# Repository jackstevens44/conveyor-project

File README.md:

# Conveyor Project

<!-- Replace this paragraph with a short description of the conveyor, what it is
designed to do, and its current development status. -->

This project is a compact conveyor system featuring a custom-designed controller PCB and 3D-printable mechanical components. I created it to gain hands-on experience with PCB design, electronics integration, mechanical design, rapid prototyping, and design-for-manufacturing.

## Project status

<!-- Examples: Planning, Prototype, Testing, or Complete. -->

**Status:** Prototype

## Repository contents

```text
conveyor-project/
├── pcb-files/                 KiCad design and fabrication files
│   ├── NewConveyorPCB.kicad_pro
│   ├── NewConveyorPCB.kicad_sch
│   ├── NewConveyorPCB.kicad_pcb
│   └── fab-files/gerbers.zip
├── stl-files/                 3D-printable mechanical parts
│   ├── conveyor-base-parts/
│   │   ├── BearingSlot.stl
│   │   ├── ConveyorBase.stl
│   │   └── MotorBase.stl
│   ├── MotorWheel.stl
│   ├── Sprocket.stl
│   ├── SprocketPin.stl
│   └── TreadLink.stl
├── code/                      Arduino code to control conveyor
└── README.md
```

## Requirements

<!-- Add versions when they are known. -->

- [KiCad](https://www.kicad.org/) to view or edit the PCB design
- A slicer and 3D printer for the STL parts
- Electronic components listed in the PCB bill of materials
- Motor, fasteners, wiring, and power supply

## Bill of materials

<!-- Replace this table with the actual parts list. Add a BOM export to
pcb-files/ if the list becomes long. -->

| Item | Quantity | Specification | Notes |
| --- | ---: | --- | --- |
| Motor | 1 | 5V DC Motor | [Digikey](https://www.digikey.com/en/products/detail/pololu/992/10449920) |
| Motor Driver | 1 | L293D | [Digikey](https://www.digikey.com/en/products/detail/stmicroelectronics/L293D/634700) |
| Arduino Nano | 1 | ABX00143 | [Digikey](https://www.digikey.com/en/products/detail/arduino/ABX00143/26766495) |
| 2 Position Terminal Blocks | 4 | TB002-599-02BE | [Digikey](https://www.digikey.com/en/products/detail/same-sky-formerly-cui-devices/TB002-500-02BE/10064069) |
| 4 Position Terminal Blocks | 3 | OSTTC042162 | [Digikey](https://www.digikey.com/en/products/detail/on-shore-technology-inc/OSTTC042162/614560) |
| Power supply | 1 | 5V DC Power Supply | [Amazon](https://www.amazon.com/Adjustable-Switching-Regulated-Adjustments-Jesverty/dp/B09YSJQWRG/ref=sr_1_9?crid=RU2I6P17LDUR&dib=eyJ2IjoiMSJ9.bpne59jAEmaTFwmIsQCQhTqgw4IQY65Dw4FDdB8OQz_Ecffxi1TowvI5zsghytbijl_1j7_s0npvxgVQFqhbWMT10DBirUDh4-yq3dJqWEhJmdyZwxivPJMaoJ1KstsehQq5iAvTCPxRA2gXOBRJsTDN7kXZ_Kgxwffos8XqOIRSXc5FngmeqCCIJYCrZ_1-oBqjrCkD9KUe5rgq8wMdk-KiZEaG6KIPqqcH2dt3D-8.EnnGaUa-Mi3bt2TU4QdSq8au0XoTXh95RY_4BBbdKmI&dib_tag=se&keywords=5v%2Bpower%2Bsupply%2Belectronics&qid=1785630137&sprefix=5v%2Bpower%2Bsupply%2Belectronics%2Caps%2C166&sr=8-9&th=1)|
| PCB | 1 | NewConveyorPCB | [JLCPCB](https://cart.jlcpcb.com/quote?stencilLayer=2&stencilWidth=100&stencilLength=100&stencilCounts=5&plateType=1&spm=Jlcpcb.Homepage.1010) |
| Conveyor base | 1 | 3D printed | `ConveyorBase.stl` |
| Motor Base | 1 | 3D printed | `MotorBase.stl` |
| Bearing slot | 4 | 3D printed | `BearingSlot.stl` |
| Motor wheel | 1 | 3D printed | `MotorWheel.stl` |
| Sprocket | 2 | 3D printed | `Sprocket.stl` |
| Sprocket pin | 2 | 3D printed | `SprocketPin.stl` |
| Tread link | 28 | 3D printed | `TreadLink.stl` |
| Ball Bearings | 4 | Any bearing that meets required dimensions | [Amazon](https://www.amazon.com/dp/B09PKD8QZZ?ref=ppx_yo2ov_dt_b_fed_asin_title&th=1) |
| Dowel Pins | 27 | 1/8" diameter 2-1/2" length | [McMaster](https://www.mcmaster.com/90145A487/) |
| Motor Band | 1 | TBD | TBD |

## Fabrication

1. Use any PCB fabrication company. JLCPCB is cheap and easy to use.

### PCB

1. Open `pcb-files/NewConveyorPCB.kicad_pro` in KiCad to review or modify the design.
2. Use `pcb-files/fab-files/gerbers.zip` when ordering the PCB.
3. Confirm the board dimensions, layer stack, drill files, and design rules with the manufacturer before ordering.

<!-- Add PCB manufacturer settings, component placement notes, and assembly
instructions here. -->

### 3D-printed parts

The printable models are in `stl-files/`.

## Assembly

<!-- Replace these placeholders with the tested assembly sequence. Photos or a
diagram are especially useful here. -->

1. Print and inspect all mechanical parts.
2. Solder components and test PCB.
3. Install the motor and motor wheel in the conveyor base.
4. Assemble the sprockets and tread links.
5. Connect the electronics and verify polarity before applying power.
6. Upload conveyor controller program to the Arduino Nano.
7. Test at low speed and adjust alignment and tension as needed.

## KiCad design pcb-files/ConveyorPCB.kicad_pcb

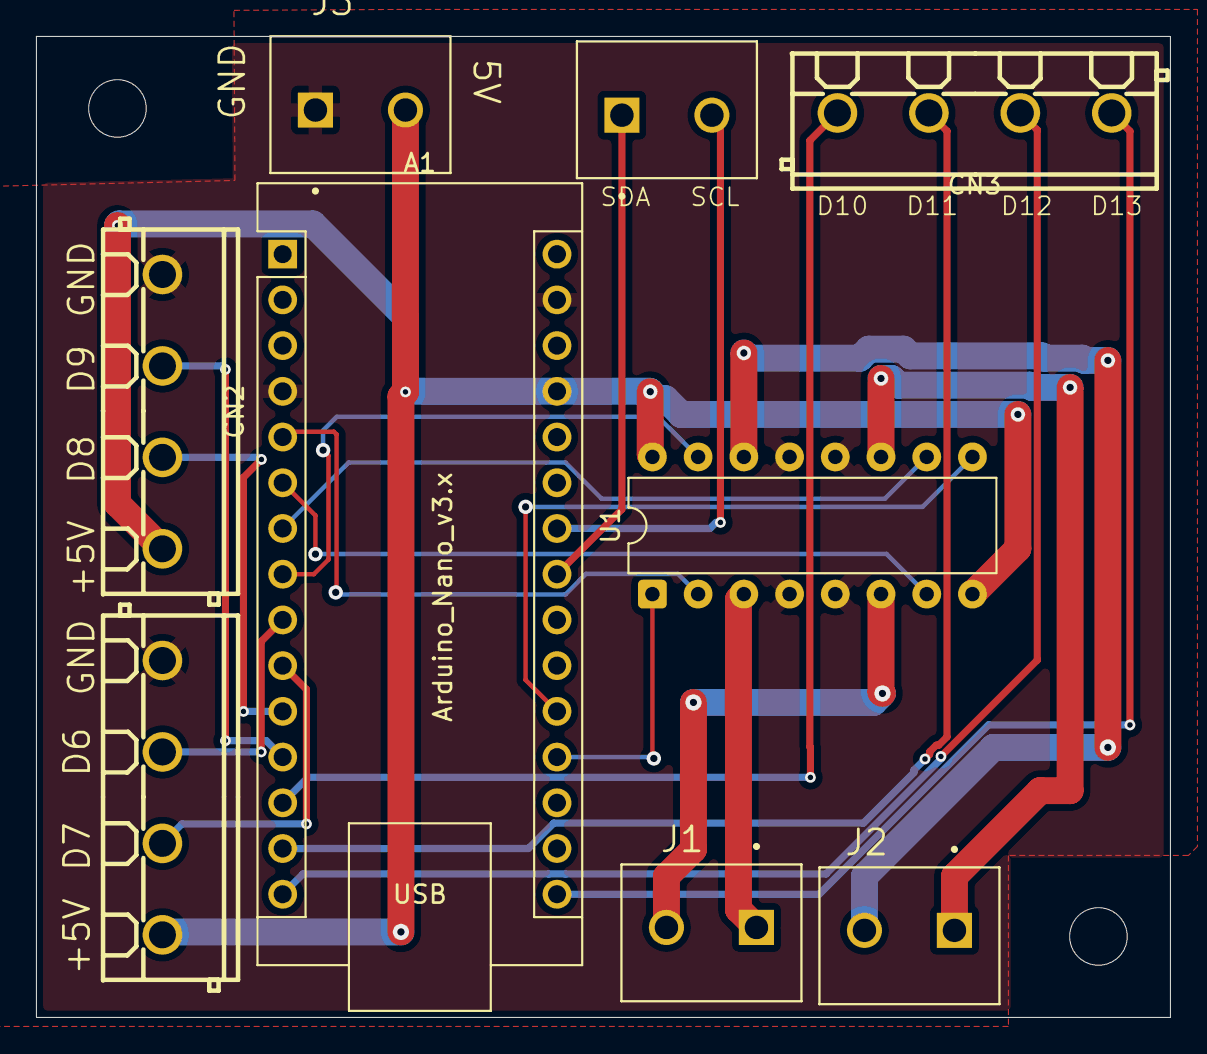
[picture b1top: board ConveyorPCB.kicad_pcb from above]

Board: 4 copper layers, 63.0 x 54.5 mm, 9 parts (0 on the bottom side), 22 nets.

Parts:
A1: Arduino_Nano_v3.x; Arduino_Nano
CN1, CN2, CN3: OSTTC042162; CONN-TH_4P-P5.08_OSTTC042162
J1: Motor 1; CUI_TB002-500-02BE
J2: Motor 2; CUI_TB002-500-02BE
J3: DO6; CUI_TB002-500-02BE
SDA1: I2C; CUI_TB002-500-02BE
U1: L293D; DIP-16_W7.62mm

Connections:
+5V: A1.27 (+5V), CN1.4, CN2.4, J3.2, U1.8 (VCC2), U1.16 (VCC1)
D10: A1.13 (D10), CN3.4
GND: A1.4 (GND), A1.29 (GND), CN1.1, CN2.1, J3.1, U1.4 (GND), U1.5 (GND), U1.12 (GND), U1.13 (GND)
unnamed: A1.19 (A0), U1.1 (EN1,2)
unnamed: A1.20 (A1), U1.9 (EN3,4)
unnamed: A1.23 (A4), SDA1.1
unnamed: A1.24 (A5), SDA1.2
unnamed: A1.5 (D2), U1.2 (1A)
unnamed: A1.6 (D3), U1.7 (2A)
unnamed: A1.7 (D4), U1.10 (3A)
unnamed: A1.8 (D5), U1.15 (4A)
unnamed: A1.9 (D6), CN1.2
unnamed: A1.10 (D7), CN1.3
unnamed: A1.11 (D8), CN2.3
unnamed: A1.12 (D9), CN2.2
unnamed: A1.14 (D11), CN3.3
unnamed: A1.15 (D12), CN3.2
unnamed: A1.16 (D13), CN3.1
unnamed: J1.1, U1.3 (1Y)
unnamed: J1.2, U1.6 (2Y)
unnamed: J2.1, U1.11 (3Y)
unnamed: J2.2, U1.14 (4Y)
